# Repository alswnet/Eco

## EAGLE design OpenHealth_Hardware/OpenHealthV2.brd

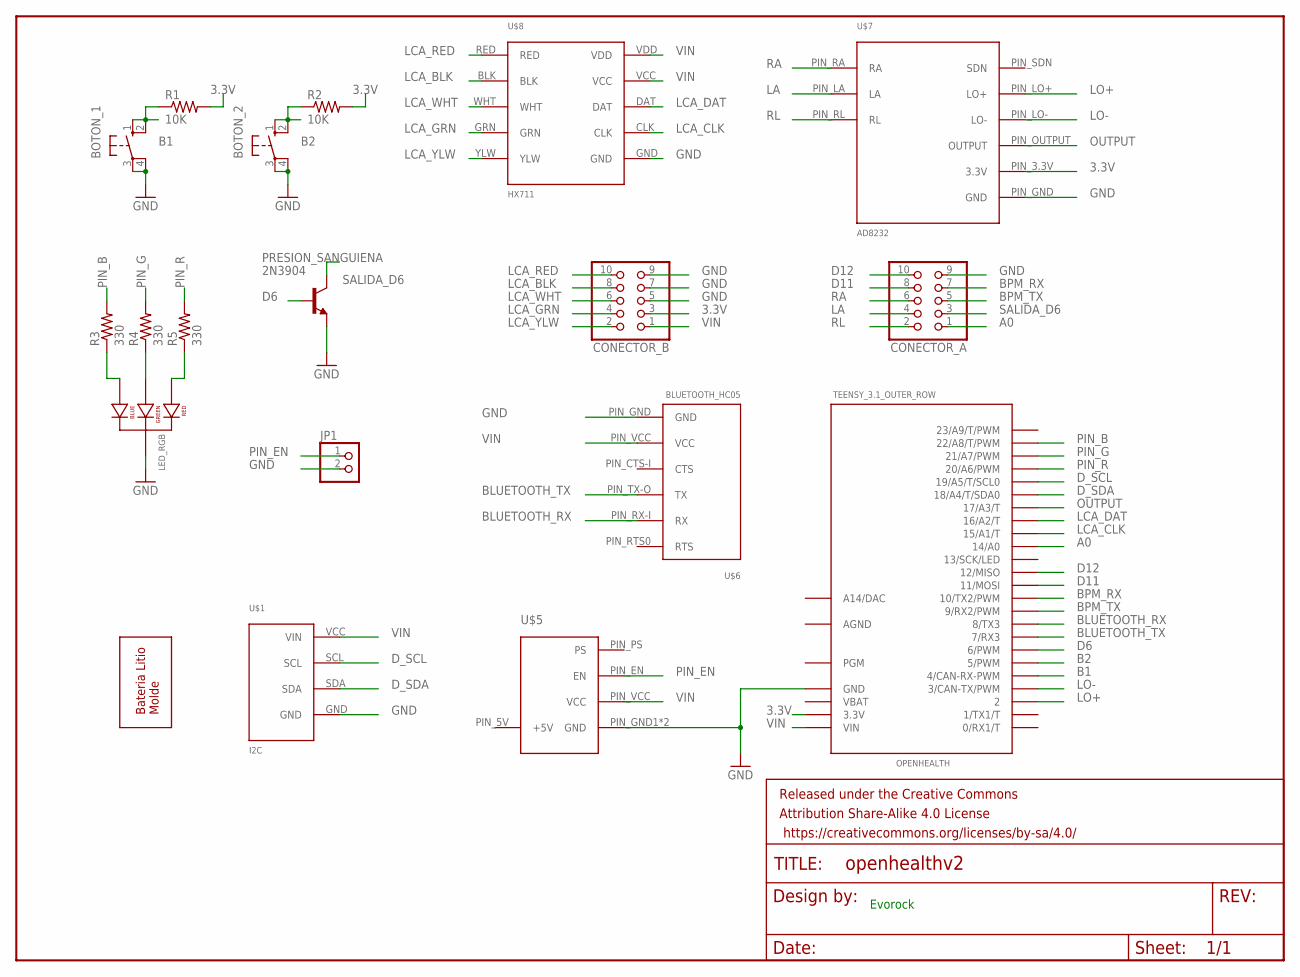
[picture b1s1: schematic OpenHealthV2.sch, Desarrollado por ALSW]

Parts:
BOTON_1, BOTON_2: B3F-10XX
CONECTOR_A: 2X05
CONECTOR_B: 2X05
FRAME1: FRAME-LETTER; CREATIVE_COMMONS
JP1: 1X02
LED_RGB: LED-RGB-CC-THRUCLEAR; LED-RGB-THRU
OPENHEALTH: TEENSY_3.1_OUTER_ROW; TEENSY3-OUTER_ROW
PRESION_SANGUIENA: 2N3904; TO92
R1, R2: 10K; 0204/7
R3, R4, R5: 330; 0204/7
U$1: I2C
U$2: BATERRY_MOLD; BATTERY_MOLD
U$5: LIPOWER
U$6: BLUETOOTH_HC05
U$7: AD8232
U$8: HX711

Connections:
3.3V: CONECTOR_B.3, OPENHEALTH.3.3V, OPENHEALTH.3.3V1 (3.3V), R1.2, R2.2, U$7.PIN_3.3V (3.3V)
A0: CONECTOR_A.1, OPENHEALTH.14/A0
AGND: OPENHEALTH.AGND
B1: BOTON_1.1 (S), BOTON_1.2 (S1), OPENHEALTH.4 (4/CAN-RX-PWM), R1.1
B2: BOTON_2.1 (S), BOTON_2.2 (S1), OPENHEALTH.5 (5/PWM), R2.1
BLUETOOTH_RX: OPENHEALTH.8 (8/TX3), U$6.PIN_RX-I (RX)
BLUETOOTH_TX: OPENHEALTH.7 (7/RX3), U$6.PIN_TX-O (TX)
BPM_RX: CONECTOR_A.7, OPENHEALTH.10 (10/TX2/PWM)
BPM_TX: CONECTOR_A.5, OPENHEALTH.9 (9/RX2/PWM)
D6: OPENHEALTH.6 (6/PWM), PRESION_SANGUIENA.2 (B)
D11: CONECTOR_A.8, OPENHEALTH.11 (11/MOSI)
D12: CONECTOR_A.10, OPENHEALTH.12 (12/MISO)
D_SCL: OPENHEALTH.19/A5 (19/A5/T/SCL0), U$1.SCL
D_SDA: OPENHEALTH.18/A4 (18/A4/T/SDA0), U$1.SDA
GND: BOTON_1.3, BOTON_1.4 (P1), BOTON_2.3, BOTON_2.4 (P1), CONECTOR_A.9, CONECTOR_B.5, CONECTOR_B.7, CONECTOR_B.9, JP1.2, LED_RGB.2 (CATHODE), OPENHEALTH.GND, OPENHEALTH.GND1 (GND), PRESION_SANGUIENA.3 (E), U$1.GND, U$5.PIN_GND1 (GND), U$5.PIN_GND2 (GND), U$6.PIN_GND (GND), U$7.PIN_GND (GND), U$8.GND
LA: CONECTOR_A.4, U$7.PIN_LA (LA)
LCA_BLK: CONECTOR_B.8, U$8.BLK
LCA_CLK: OPENHEALTH.15/A1 (15/A1/T), U$8.CLK
LCA_DAT: OPENHEALTH.16/A2 (16/A2/T), U$8.DAT
LCA_GRN: CONECTOR_B.4, U$8.GRN
LCA_RED: CONECTOR_B.10, U$8.RED
LCA_WHT: CONECTOR_B.6, U$8.WHT
LCA_YLW: CONECTOR_B.2, U$8.YLW
LO+: OPENHEALTH.2, U$7.PIN_LO+ (LO+)
LO-: OPENHEALTH.3 (3/CAN-TX/PWM), U$7.PIN_LO- (LO-)
unnamed: LED_RGB.4 (BLUE_CATHODE), R3.1
unnamed: LED_RGB.1 (RED_CATHODE), R5.1
unnamed: LED_RGB.3 (GREEN_CATHODE), R4.1
OUTPUT: OPENHEALTH.17/A3 (17/A3/T), U$7.PIN_OUTPUT (OUTPUT)
PIN_B: OPENHEALTH.22/A8 (22/A8/T/PWM), R3.2
PIN_EN: JP1.1, U$5.PIN_EN (EN)
PIN_G: OPENHEALTH.21/A7 (21/A7/PWM), R4.2
PIN_R: OPENHEALTH.20/A6 (20/A6/PWM), R5.2
RA: CONECTOR_A.6, U$7.PIN_RA (RA)
RL: CONECTOR_A.2, U$7.PIN_RL (RL)
SALIDA_D6: CONECTOR_A.3, PRESION_SANGUIENA.1 (C)
VBAT: OPENHEALTH.VBAT
VIN: CONECTOR_B.1, OPENHEALTH.VIN, U$1.VCC (VIN), U$5.PIN_VCC (VCC), U$6.PIN_VCC (VCC), U$8.VCC, U$8.VDD

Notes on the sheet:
Evorock

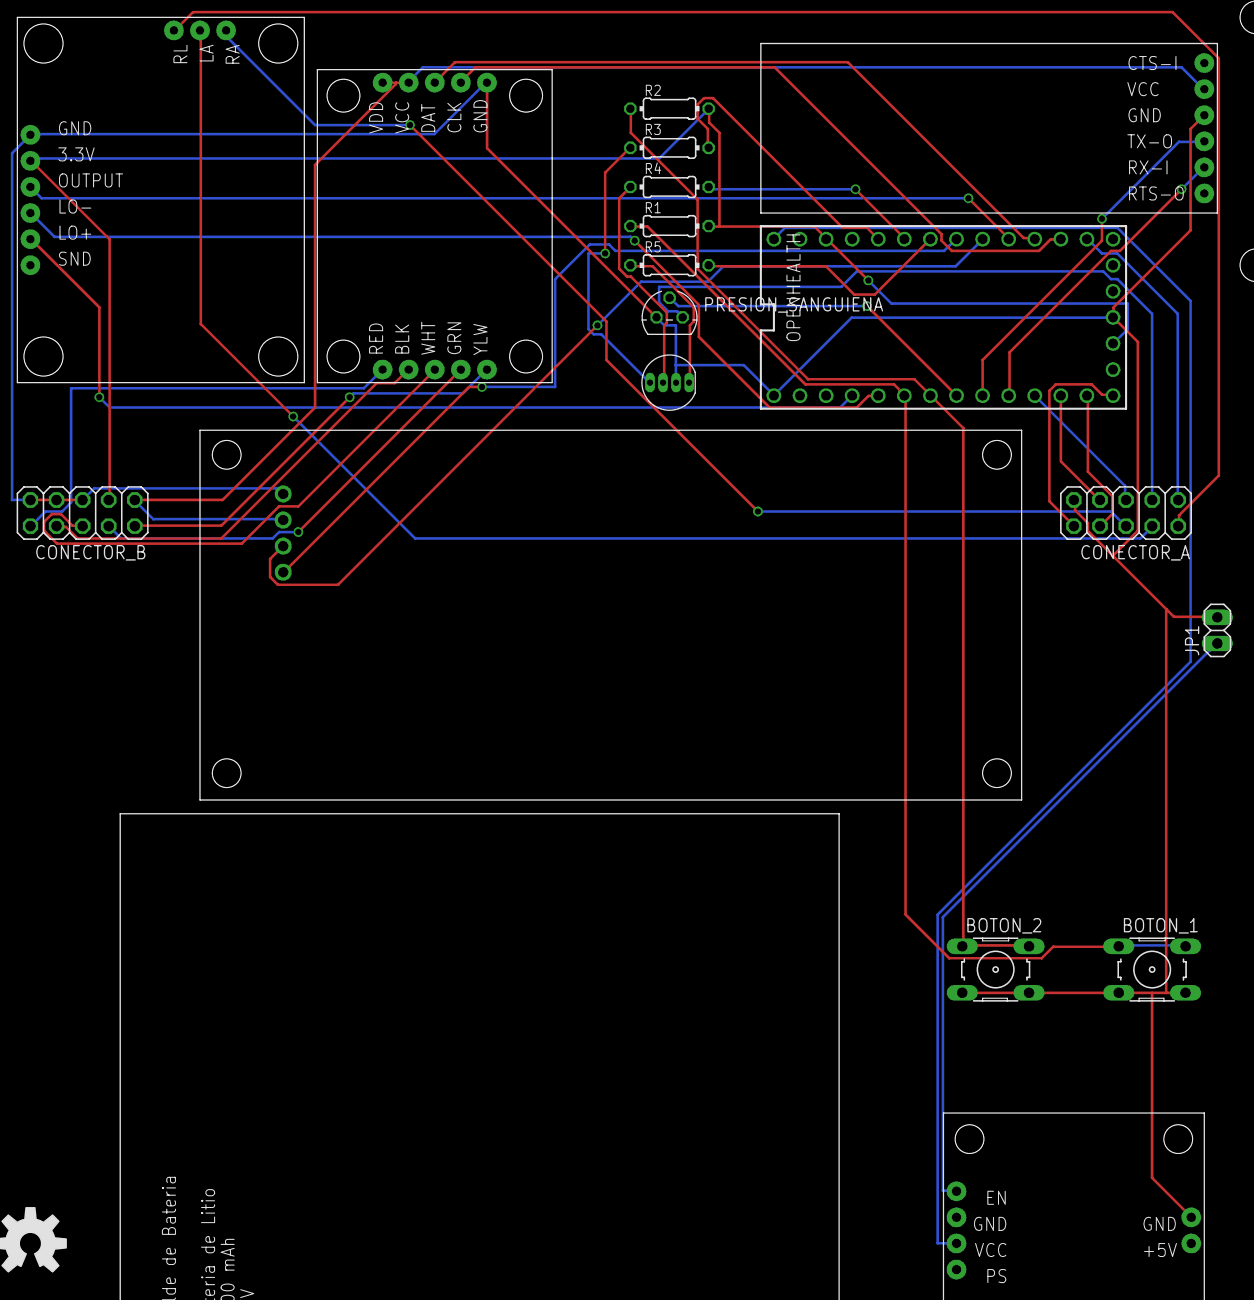
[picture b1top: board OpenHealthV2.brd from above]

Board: 2 copper layers, 21 parts (0 on the bottom side), 36 nets.

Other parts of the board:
U$3: OSHW-LOGO-L

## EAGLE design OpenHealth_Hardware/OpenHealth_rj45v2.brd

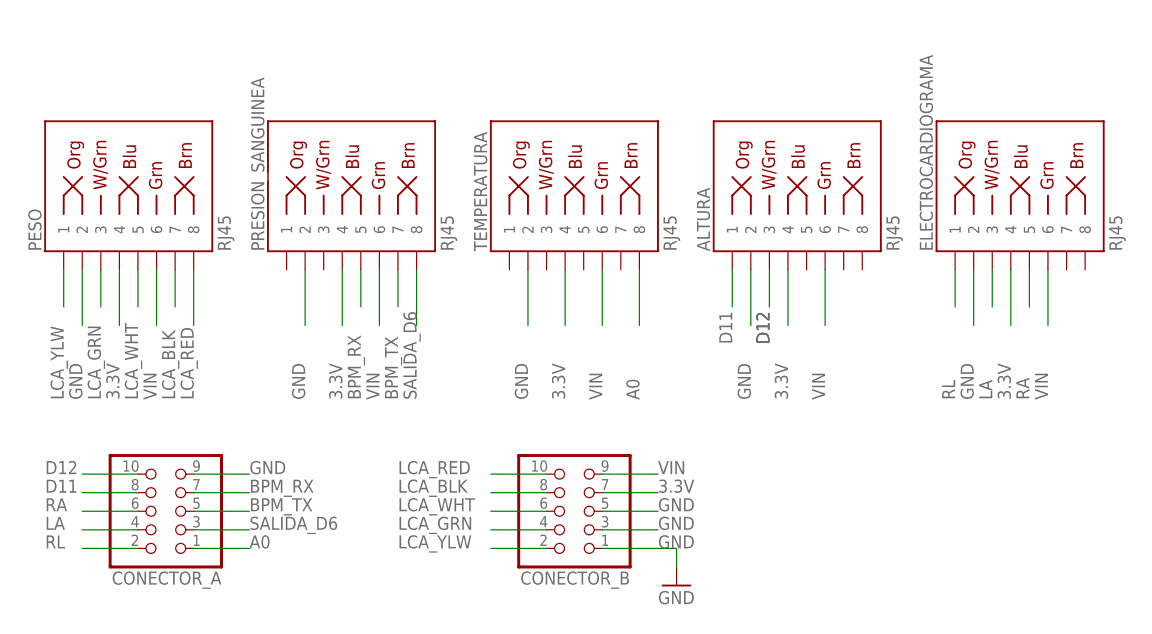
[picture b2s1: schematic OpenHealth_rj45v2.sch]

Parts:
ALTURA: RJ45; RJ45-8
CONECTOR_A: PINHD-2X5; 2X05
CONECTOR_B: PINHD-2X5; 2X05
ELECTROCARDIOGRAMA: RJ45; RJ45-8
PESO: RJ45; RJ45-8
PRESION_SANGUINEA: RJ45; RJ45-8
TEMPERATURA: RJ45; RJ45-8

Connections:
3.3V: ALTURA.4, CONECTOR_B.7, ELECTROCARDIOGRAMA.4, PESO.4, PRESION_SANGUINEA.4, TEMPERATURA.4
A0: CONECTOR_A.1, TEMPERATURA.8
BPM_RX: CONECTOR_A.7, PRESION_SANGUINEA.5
BPM_TX: CONECTOR_A.5, PRESION_SANGUINEA.7
D11: ALTURA.1, CONECTOR_A.8
D12: ALTURA.3, CONECTOR_A.10
GND: ALTURA.2, CONECTOR_A.9, CONECTOR_B.1, CONECTOR_B.3, CONECTOR_B.5, ELECTROCARDIOGRAMA.2, PESO.2, PRESION_SANGUINEA.2, TEMPERATURA.2
LA: CONECTOR_A.4, ELECTROCARDIOGRAMA.3
LCA_BLK: CONECTOR_B.8, PESO.7
LCA_GRN: CONECTOR_B.4, PESO.3
LCA_RED: CONECTOR_B.10, PESO.8
LCA_WHT: CONECTOR_B.6, PESO.5
LCA_YLW: CONECTOR_B.2, PESO.1
RA: CONECTOR_A.6, ELECTROCARDIOGRAMA.5
RL: CONECTOR_A.2, ELECTROCARDIOGRAMA.1
SALIDA_D6: CONECTOR_A.3, PRESION_SANGUINEA.8
VIN: ALTURA.6, CONECTOR_B.9, ELECTROCARDIOGRAMA.6, PESO.6, PRESION_SANGUINEA.6, TEMPERATURA.6

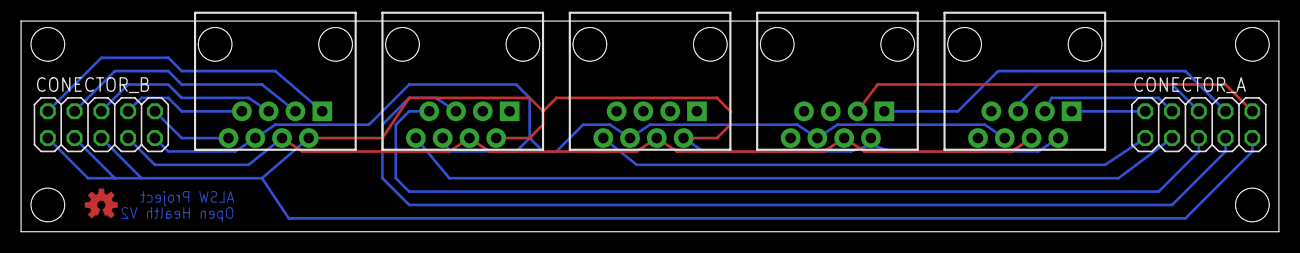
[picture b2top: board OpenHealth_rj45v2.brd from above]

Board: 2 copper layers, 119.4 x 20.0 mm, 8 parts (0 on the bottom side), 17 nets.

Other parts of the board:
U$1: OSHW-LOGO-S_COPPER

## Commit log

2016-05-19 Agregando librerias del Libelium Escudo de Sensores Biometricos Se ponen a la dispobilidad las librerias para futuras ediciones mas info en: https://www.cooking-hacks.com/documentation/tutorials/ehea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
2016-09-07 Reparando la libreria pasa hacerlo compatible con los arduinoIDE actuales
2016-09-08 Codigo de Inicio del proyecto
2016-09-08 Cambiando nombre y remobiendo librerias viejas
2016-09-08 Desarrollo del escudo de OpenHealth, basado en un Teensy 3.1, que lograra medir Temperatura Corporal, Ritmo Cardiaco, Presion Sanguinea, Peso y Altura, contara con una pantalla LCD con comunicacion I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
2016-09-08 Agregando descripciones de conecion de pines del teensy
2016-09-08 Se termino el enrutado de las conexiones y se le agrego nombre a los componentes
2016-09-08 Correcion de botones, configuracion pull up, se le asigno valor a las resistencias
2016-09-08 Creacion del PCB board y simulacion de los componentes que iran abordo del circuito, PCB board sin enrutar.
2016-09-08 Generacion de la imagen en formato png del PCB board.
2016-09-08 Creacion de los agujeros del modulo de carga
2016-09-09 Creacion de espacios, se empezara a ordenar y ubicar a donde iran los componentes
2016-09-09 Modificacion del archivo conexion, agregando las funciones que realizara el proyecto
2016-09-09 Creacion de la tarjeta secundaria de openhealth, en ella iran los conectores rj45 para conectar los sensores externos
2016-09-11 Eliminacion de archivos de cache, enrutado logico de las salidas del rj45, modificacion del archivo planteando mejoras
2016-09-11 Eliminacion de archivos de cache
2016-09-12 Enrutado del de la placa de los conectores del RJ45 y se comienzo del proceso de ordenamiento de la placa principal
2016-09-12 Borrado de archivo cache de eagle
2016-09-23 Reduccion de la placa madre, se agrego las resistencias faltantes del led y se ordeno previo al enrutado
2016-09-24 Agregando archivos a inorar en eagle
2016-09-24 Eliminacion de archivos temporales de egale
2016-10-18 se añadio el git ignore se trabajo en un escudo version oshpark y se sigue trabajando en la tarjeta principal
2016-10-18 se elimino carpeta duplicada
2016-10-18 Adjunto imagen en 3D del pcb board
2016-10-18 Reparacion de placa principal - modo demo
2016-10-26 Creacion de la Primera Libreria
2016-10-26 Creacion de los modulos de bluetooth y ad8232 asi como el cambio de nombre de la libreria y la utilizacion de la libreria en el proyecto
2016-10-27 Finalizacion de la primera version, listo para revision

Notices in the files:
parts and their libraries:
SparkFun-LED: Licensing: Creative Commons ShareAlike 4.0 International - https://creativecommons.org/licenses/by-sa/4.0
SparkFun-Aesthetics: Released under the Creative Commons Attribution Share-Alike 4.0 License
SparkFun-Aesthetics: https://creativecommons.org/licenses/by-sa/4.0
